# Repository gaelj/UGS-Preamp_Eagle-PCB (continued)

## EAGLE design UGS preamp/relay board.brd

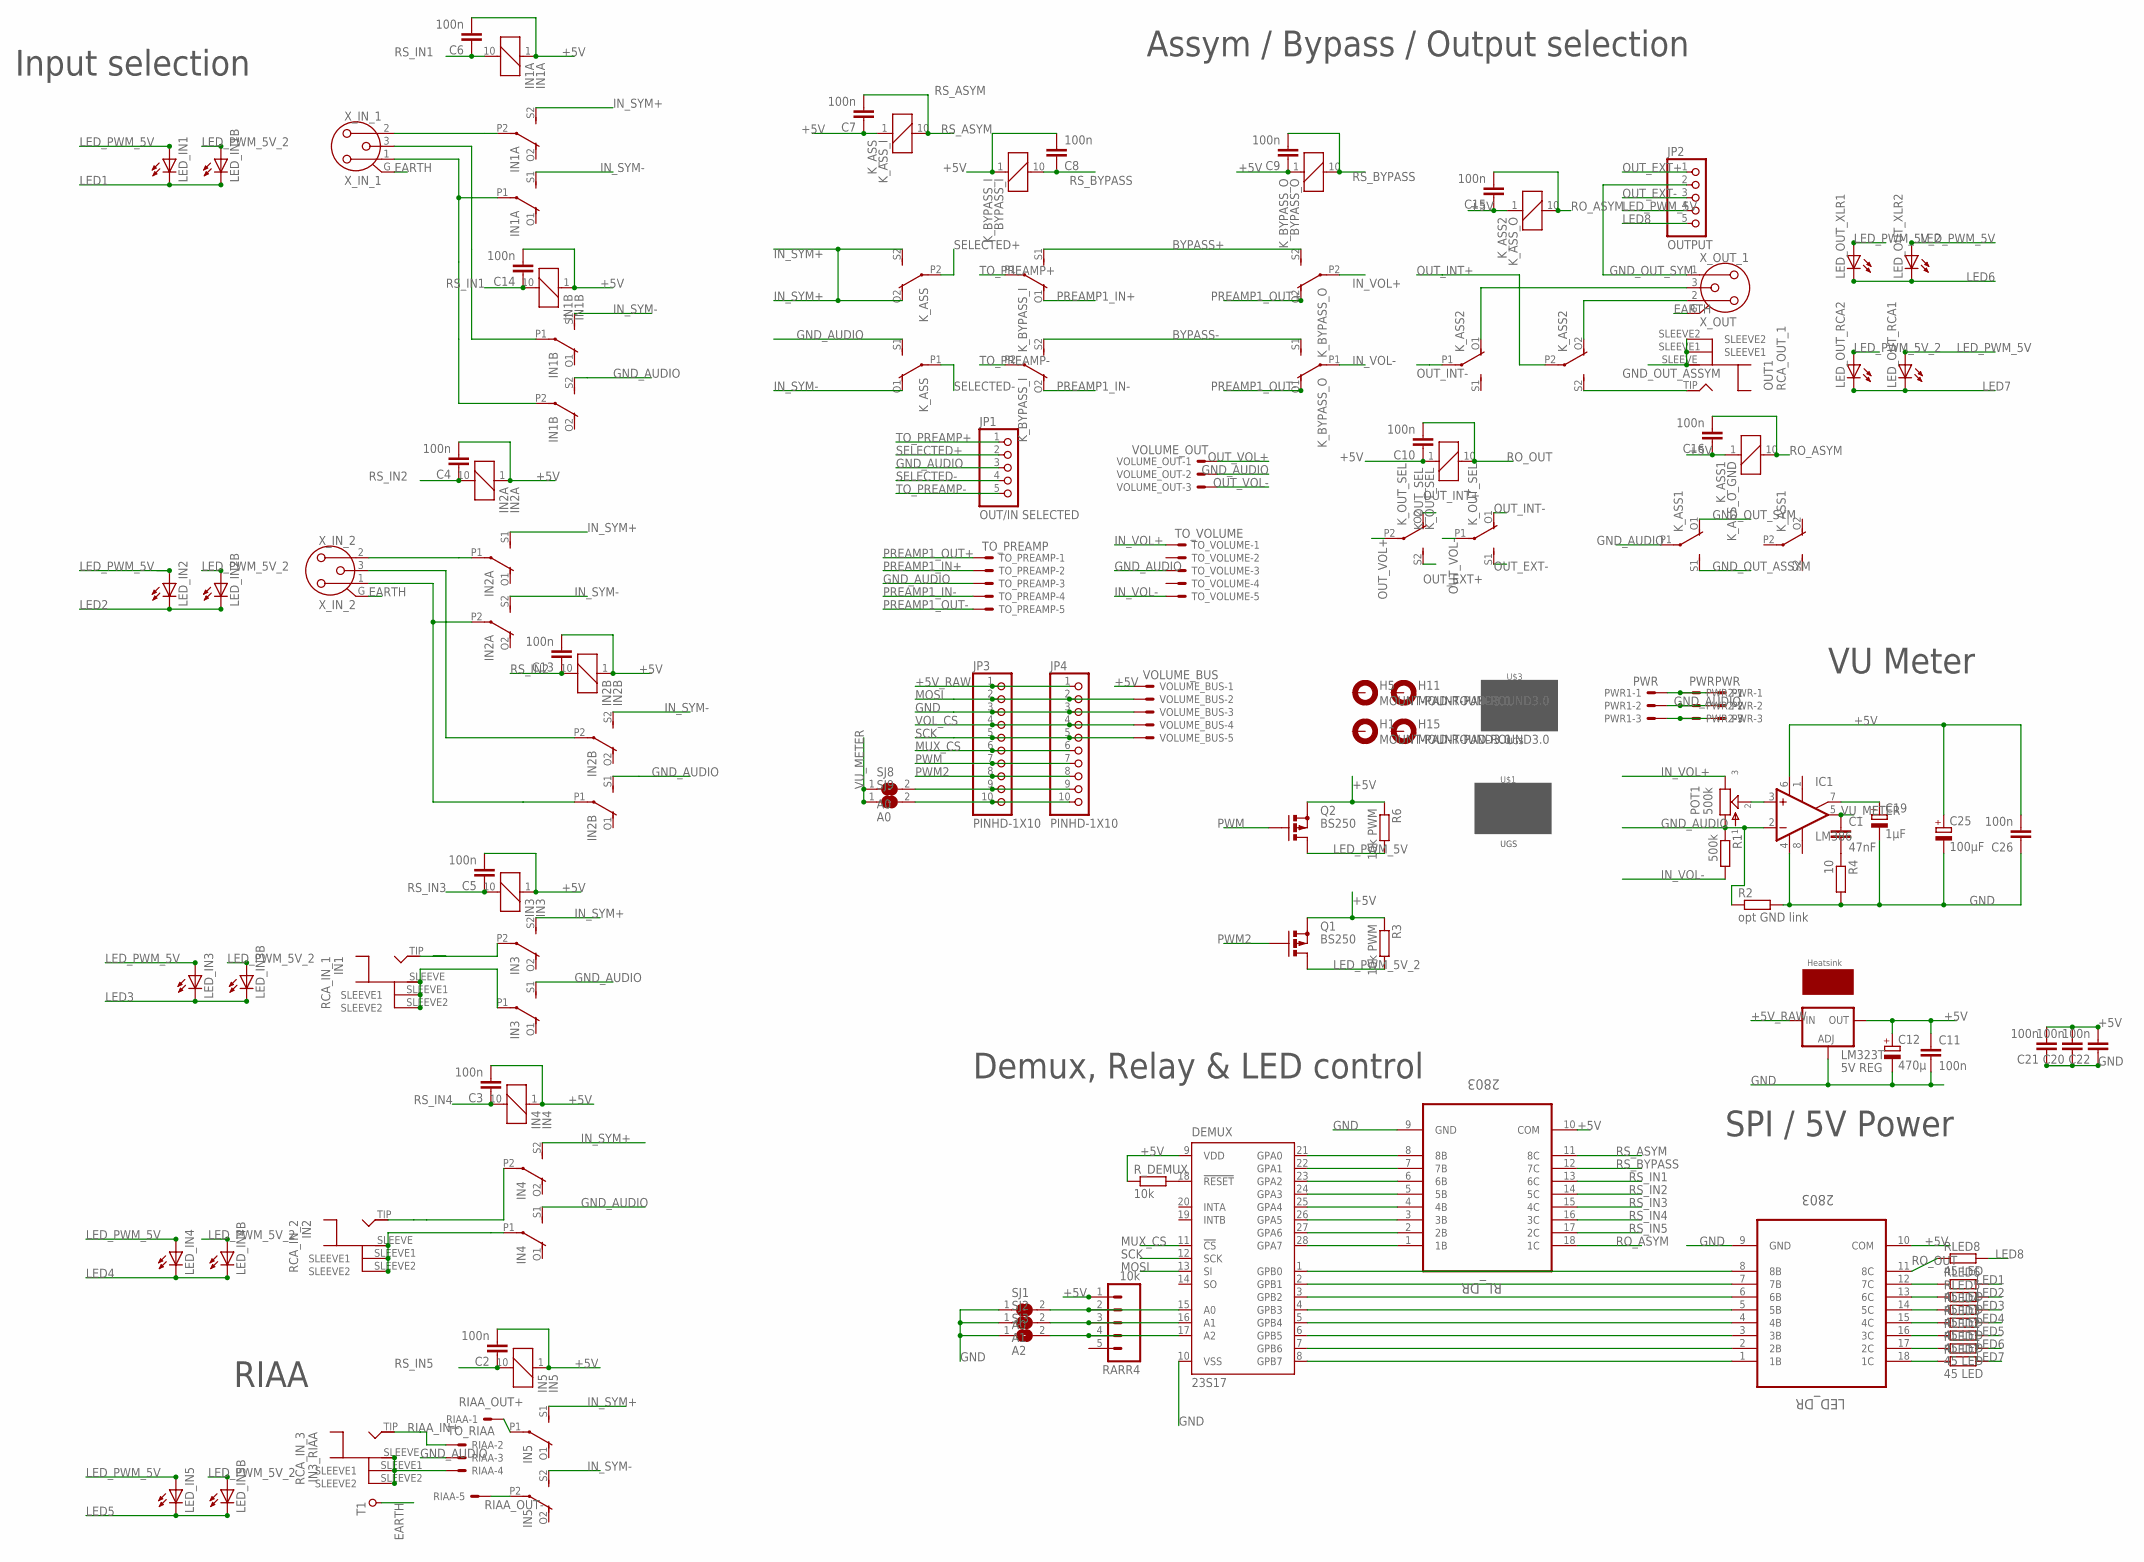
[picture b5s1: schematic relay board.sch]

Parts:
C1: 47nF; C5B3
C2, C3, C4, C5, C6, C7, C8, C9, C10, C11, C13, C14, C15, C16, C20, C21, C22, C26: 100n; C050-025X075
C12: 470µ; E2,5-6
C19: 1µF; E2,5-5
C25: 100µF; E5-6
DEMUX: 23S17; SO28W; MPN MCP23S17-E/SO
H1, H5, H11, H15: MOUNT-PAD-ROUND3.0; 3,0-PAD
IC1: LM386; DIL08
IN1A: IN1A; G6H2-100
IN1B: IN1B; G6H2-100
IN2A: IN2A; G6H2-100
IN2B: IN2B; G6H2-100
IN3: IN3; G6H2-100
IN4: IN4; G6H2-100
IN5: IN5; G6H2-100
JP1: OUT/IN SELECTED; 1X05
JP2: OUTPUT; 1X05
JP3, JP4: PINHD-1X10; 1X10-BIG
K_ASS: K_ASS_I; G6H2-100
K_ASS1: K_ASS_O_GND; G6H2-100
K_ASS2: K_ASS_O; G6H2-100
K_BYPASS_I: BYPASS_I; G6H2-100
K_BYPASS_O: BYPASS_O; G6H2-100
K_OUT_SEL: K_OUT_SEL; G6H2-100
LED_DR: 2803; SOIC127P1030X265-18N; MPN ULN2803ADWR
LED_IN1, LED_IN1B, LED_IN2, LED_IN2B, LED_IN3, LED_IN3B, LED_IN4, LED_IN4B, LED_IN5, LED_IN5B: TLLG4400; LED3MM
LED_OUT_RCA1, LED_OUT_RCA2: TLLG4400; LED3MM
LED_OUT_XLR1, LED_OUT_XLR2: TLLG4400; LED3MM
LM323T: 5V REG; TO220S
POT1: 500k; B25P
PWR, PWR1, PWR2: PWR; 70543-03
Q1, Q2: BS250; SOT54E
R1: 500k; 0207/7
R2: opt GND link; 0207/10
R3, R6: 10k PWM; 0207/10
R4: 10; 0207/10
RARR4: 10k; 1X05
RCA_IN_1: IN1; MONO_JACK
RCA_IN_2: IN2; MONO_JACK
RCA_IN_3: IN3_RIAA; MONO_JACK
RCA_OUT_1: OUT1; MONO_JACK
RIAA: TO_RIAA; 70543-05
RLED1, RLED2, RLED3, RLED4, RLED5, RLED6, RLED7, RLED8: 45 LED; 0207/10
RL_DR: 2803; SOIC127P1030X265-18N
R_DEMUX: 10k; RTH025W
SJ1, SJ8, SJ9: A0; SJ
SJ2: A1; SJ
SJ3: A2; SJ
T1: PAD_TERMINAL-1.02MM_SQUARE; CON_PAD_SQUARE_1.02MM
TO_PREAMP: TO_PREAMP; 70543-05
TO_VOLUME: TO_VOLUME; 70543-05
U$1, U$3: UGS
U$4: HEATSINK
VOLUME_BUS: VOLUME_BUS; 70543-05
VOLUME_OUT: VOLUME_OUT; 70543-03
X_IN_1: X_IN_1; NC3FAH2
X_IN_2: X_IN_2; NC3FAH2
X_OUT_1: X_OUT; NC3MBH

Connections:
+5V: C2.2, C3.2, C4.2, C5.2, C6.2, C7.1, C8.2, C9.1, C10.1, C11.1, C12.+, C13.2, C14.2, C15.1, C16.1, C20.2, C21.2, C22.2, C25.+, C26.2, DEMUX.9 (VDD), IC1.6 (V+), IN1A.1, IN1B.1, IN2A.1, IN2B.1, IN3.1, IN4.1, IN5.1, K_ASS.1, K_ASS1.1, K_ASS2.1, K_BYPASS_I.1, K_BYPASS_O.1, K_OUT_SEL.1, LED_DR.10 (COM), LM323T.3 (OUT), Q1.S, Q2.S, R3.1, R6.1, RARR4.1, RL_DR.10 (COM), R_DEMUX.1, VOLUME_BUS.1
+5V_RAW: JP3.1, JP4.1, LM323T.1 (IN)
BYPASS+: K_BYPASS_I.S1 (S), K_BYPASS_O.S2 (S)
BYPASS-: K_BYPASS_I.S2 (S), K_BYPASS_O.S1 (S)
EARTH: T1.P, X_IN_1.G, X_IN_2.G, X_OUT_1.G
GND: C11.2, C12.-, C19.-, C20.1, C21.1, C22.1, C25.-, C26.1, DEMUX.10 (VSS), IC1.4 (V-), JP3.3, JP4.3, LED_DR.9 (GND), LM323T.2 (ADJ), R2.2, R4.2, RL_DR.9 (GND), SJ1.1, SJ2.1, SJ3.1, VOLUME_BUS.3
GND_AUDIO: IC1.2 (-IN), IN1B.S2 (S), IN2B.S1 (S), IN3.S1 (S), IN4.S1 (S), JP1.3, K_ASS.S1 (S), K_ASS1.P1, POT1.1, PWR.2, PWR1.2, PWR2.2, R1.1, R2.1, RIAA.3, TO_PREAMP.3, TO_VOLUME.3, VOLUME_OUT.2
GND_IN_RIAA: RCA_IN_3.SLEEVE, RCA_IN_3.SLEEVE1, RCA_IN_3.SLEEVE2, RIAA.4
GND_OUT_ASSYM: K_ASS1.S1 (S), RCA_OUT_1.SLEEVE, RCA_OUT_1.SLEEVE1, RCA_OUT_1.SLEEVE2
GND_OUT_SYM: JP2.2, K_ASS1.O1 (O), X_OUT_1.1
IN_SYM+: IN1A.S2 (S), IN2A.S1 (S), IN3.S2 (S), IN4.S2 (S), IN5.S1 (S), K_ASS.O2 (O), K_ASS.S2 (S)
IN_SYM-: IN1A.S1 (S), IN1B.S1 (S), IN2A.S2 (S), IN2B.S2 (S), IN5.S2 (S), K_ASS.O1 (O)
IN_VOL+: K_BYPASS_O.P2, POT1.3, TO_VOLUME.1
IN_VOL-: K_BYPASS_O.P1, R1.2, TO_VOLUME.5
LED1: LED_IN1.K (C), LED_IN1B.K (C), RLED6.2
LED2: LED_IN2.K (C), LED_IN2B.K (C), RLED5.2
LED3: LED_IN3.K (C), LED_IN3B.K (C), RLED4.2
LED4: LED_IN4.K (C), LED_IN4B.K (C), RLED3.2
LED5: LED_IN5.K (C), LED_IN5B.K (C), RLED2.2
LED6: LED_OUT_XLR1.K (C), LED_OUT_XLR2.K (C), RLED1.2
LED7: LED_OUT_RCA1.K (C), LED_OUT_RCA2.K (C), RLED7.2
LED8: JP2.5, RLED8.2
LED_PWM_5V: JP2.4, LED_IN1.A, LED_IN2.A, LED_IN3.A, LED_IN4.A, LED_IN5.A, LED_OUT_RCA1.A, LED_OUT_XLR2.A, Q2.D, R6.2
LED_PWM_5V_2: LED_IN1B.A, LED_IN2B.A, LED_IN3B.A, LED_IN4B.A, LED_IN5B.A, LED_OUT_RCA2.A, LED_OUT_XLR1.A, Q1.D, R3.2
MOSI: DEMUX.13 (SI), JP3.2, JP4.2, VOLUME_BUS.2
MUX_CS: DEMUX.11 (!CS), JP3.6, JP4.6
unnamed: DEMUX.18 (!RESET), R_DEMUX.2
unnamed: LED_DR.17 (2C), RLED1.1
unnamed: IN3.P2, RCA_IN_1.TIP
unnamed: C1.2, R4.1
unnamed: PWR.1, PWR1.1, PWR2.1
unnamed: LED_DR.18 (1C), RLED7.1
unnamed: IC1.3 (+IN), POT1.2
unnamed: LED_DR.16 (3C), RLED2.1
unnamed: C19.+, IC1.7 (BYPASS)
unnamed: JP3.10, JP4.10, SJ9.2
unnamed: DEMUX.8 (GPB7), LED_DR.1 (1B)
unnamed: DEMUX.7 (GPB6), LED_DR.2 (2B)
unnamed: DEMUX.6 (GPB5), LED_DR.3 (3B)
unnamed: DEMUX.5 (GPB4), LED_DR.4 (4B)
unnamed: DEMUX.4 (GPB3), LED_DR.5 (5B)
unnamed: DEMUX.3 (GPB2), LED_DR.6 (6B)
unnamed: DEMUX.2 (GPB1), LED_DR.7 (7B)
unnamed: DEMUX.1 (GPB0), LED_DR.8 (8B)
unnamed: LED_DR.15 (4C), RLED3.1
unnamed: PWR.3, PWR1.3, PWR2.3
unnamed: IN4.P1, RCA_IN_2.SLEEVE, RCA_IN_2.SLEEVE1, RCA_IN_2.SLEEVE2
unnamed: IN2A.P1, X_IN_2.2 (1)
unnamed: IN2B.P2, X_IN_2.3
unnamed: IN2A.P2, IN2B.P1, X_IN_2.1 (2)
unnamed: LED_DR.14 (5C), RLED4.1
unnamed: LED_DR.13 (6C), RLED5.1
unnamed: LED_DR.12 (7C), RLED6.1
unnamed: IN4.P2, RCA_IN_2.TIP
unnamed: DEMUX.15 (A0), RARR4.2, SJ1.2
unnamed: DEMUX.16 (A1), RARR4.3, SJ2.2
unnamed: IN3.P1, RCA_IN_1.SLEEVE, RCA_IN_1.SLEEVE1, RCA_IN_1.SLEEVE2
unnamed: IN1A.P2, X_IN_1.2 (1)
unnamed: IN1B.P1, X_IN_1.3
unnamed: DEMUX.17 (A2), RARR4.4, SJ3.2
unnamed: IN1A.P1, IN1B.P2, X_IN_1.1 (2)
unnamed: K_ASS2.O2 (O), X_OUT_1.2
unnamed: K_ASS2.S2 (S), RCA_OUT_1.TIP
unnamed: DEMUX.21 (GPA0), RL_DR.8 (8B)
unnamed: DEMUX.22 (GPA1), RL_DR.7 (7B)
unnamed: DEMUX.23 (GPA2), RL_DR.6 (6B)
unnamed: DEMUX.24 (GPA3), RL_DR.5 (5B)
unnamed: DEMUX.25 (GPA4), RL_DR.4 (4B)
unnamed: DEMUX.26 (GPA5), RL_DR.3 (3B)
unnamed: DEMUX.27 (GPA6), RL_DR.2 (2B)
unnamed: DEMUX.28 (GPA7), RL_DR.1 (1B)
unnamed: K_ASS2.O1 (O), X_OUT_1.3
unnamed: JP3.9, JP4.9, SJ8.2
OUT_EXT+: JP2.1, K_OUT_SEL.S2 (S)
OUT_EXT-: JP2.3, K_OUT_SEL.S1 (S)
OUT_INT+: K_ASS2.P2, K_OUT_SEL.O2 (O)
OUT_INT-: K_ASS2.P1, K_OUT_SEL.O1 (O)
OUT_VOL+: K_OUT_SEL.P2, VOLUME_OUT.1
OUT_VOL-: K_OUT_SEL.P1, VOLUME_OUT.3
PREAMP1_IN+: K_BYPASS_I.O1 (O), TO_PREAMP.2
PREAMP1_IN-: K_BYPASS_I.O2 (O), TO_PREAMP.4
PREAMP1_OUT+: K_BYPASS_O.O2 (O), TO_PREAMP.1
PREAMP1_OUT-: K_BYPASS_O.O1 (O), TO_PREAMP.5
PWM: JP3.7, JP4.7, Q2.G
PWM2: JP3.8, JP4.8, Q1.G
RIAA_IN+: RCA_IN_3.TIP, RIAA.2
RIAA_OUT+: IN5.P1, RIAA.1
RIAA_OUT-: IN5.P2, RIAA.5
RO_ASYM: C15.2, C16.2, K_ASS1.10 (2), K_ASS2.10 (2), RL_DR.18 (1C)
RO_OUT: C10.2, K_OUT_SEL.10 (2), LED_DR.11 (8C), RLED8.1
RS_ASYM: C7.2, K_ASS.10 (2), RL_DR.11 (8C)
RS_BYPASS: C8.1, C9.2, K_BYPASS_I.10 (2), K_BYPASS_O.10 (2), RL_DR.12 (7C)
RS_IN1: C6.1, C14.1, IN1A.10 (2), IN1B.10 (2), RL_DR.13 (6C)
RS_IN2: C4.1, C13.1, IN2A.10 (2), IN2B.10 (2), RL_DR.14 (5C)
RS_IN3: C5.1, IN3.10 (2), RL_DR.15 (4C)
RS_IN4: C3.1, IN4.10 (2), RL_DR.16 (3C)
RS_IN5: C2.1, IN5.10 (2), RL_DR.17 (2C)
SCK: DEMUX.12 (SCK), JP3.5, JP4.5, VOLUME_BUS.5
SELECTED+: JP1.2, K_ASS.P2
SELECTED-: JP1.4, K_ASS.P1
TO_PREAMP+: JP1.1, K_BYPASS_I.P1
TO_PREAMP-: JP1.5, K_BYPASS_I.P2
VOL_CS: JP3.4, JP4.4, VOLUME_BUS.4
VU_METER: C1.1, IC1.5 (OUT), SJ8.1, SJ9.1

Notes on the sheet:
Assym / Bypass / Output selection
SPI / 5V Power
Demux, Relay & LED control
Input selection
RIAA
VU Meter

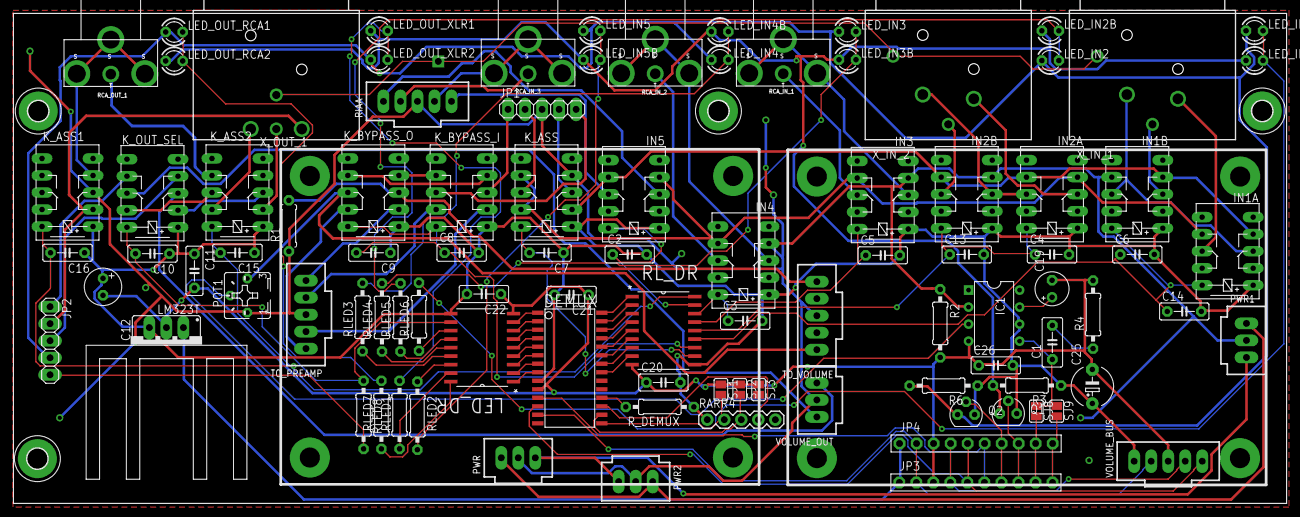
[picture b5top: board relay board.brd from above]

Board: 2 copper layers, 190.1 x 73.2 mm, 104 parts (0 on the bottom side), 104 nets.

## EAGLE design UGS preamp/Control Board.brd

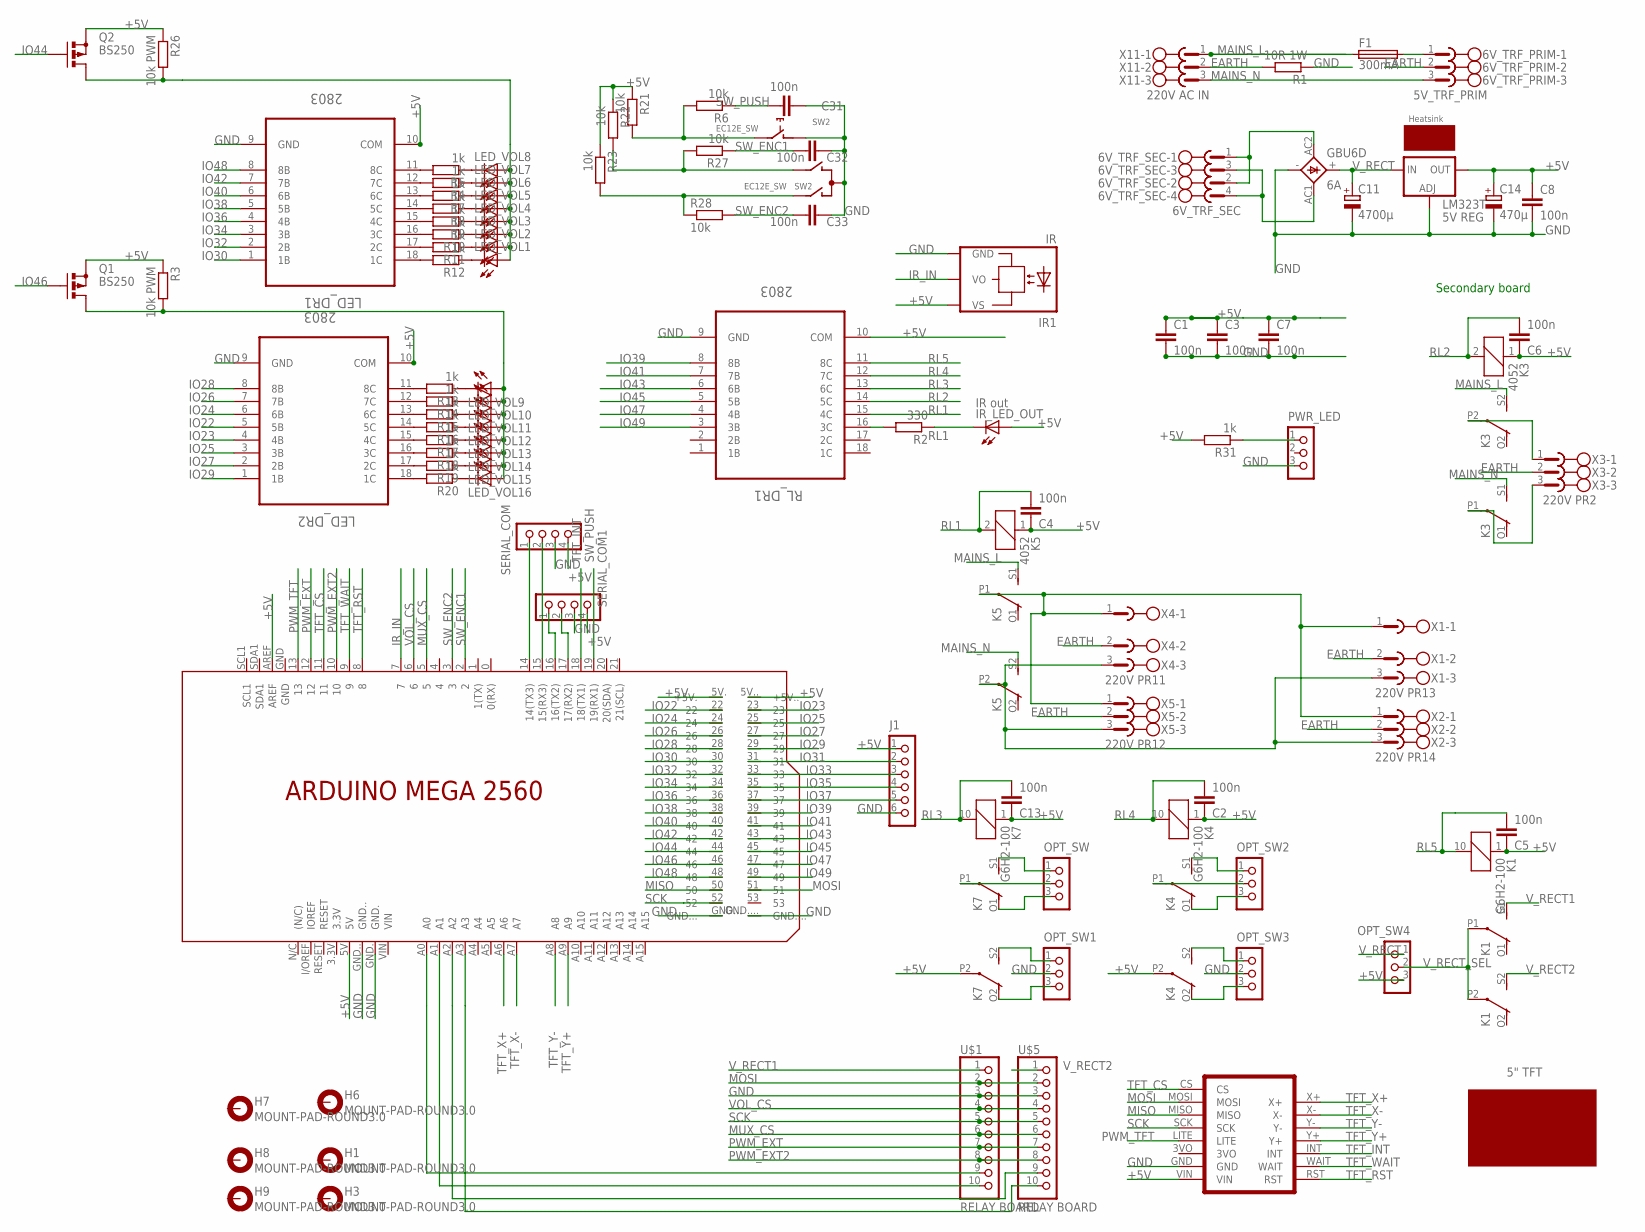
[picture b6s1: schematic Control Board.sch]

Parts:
6V_TRF_PRIM: 5V_TRF_PRIM; MSTBV3; MPN MSTBV 2,5/3-GF-5.08
6V_TRF_SEC: 6V_TRF_SEC; MSTBV4
C1, C2, C3, C4, C5, C6, C7, C8, C13, C31, C32, C33: 100n; C050-025X075
C11: 4700µ; E7,5-16
C14: 470µ; E2,5-6
F1: 300mA; GSH15
GBU6D: 6A; GBU4S
H1, H3, H6, H7, H8, H9: MOUNT-PAD-ROUND3.0; 3,0-PAD
IR1: IR; TSOP17_TB1
IR_LED_OUT: IR out; LED3MM
J1: CON_HEADER_1X06-PTH; M1X6
K1, K4, K7: G6H2-100
K3, K5: 4052; F4052
LED_DR1, LED_DR2: 2803; SOIC127P1030X265-18N; MPN ULN2803ADWR
LED_VOL1, LED_VOL2, LED_VOL3, LED_VOL4, LED_VOL5, LED_VOL6, LED_VOL7, LED_VOL8, LED_VOL9, LED_VOL10, LED_VOL11, LED_VOL12, LED_VOL13, LED_VOL14, LED_VOL15, LED_VOL16: TLLG4400; LED3MM
LM323T: 5V REG; TO220S
OPT_SW, OPT_SW1, OPT_SW2, OPT_SW3: CON_HEADER_1X03-PTH; M1X3
OPT_SW4: V_RECT_-_5V_OUT; M1X3
PCB2: ARDUINO_MEGA2560_INV
PWR_LED: CON_HEADER_1X03-PTH; M1X3
Q1, Q2: BS250; SOT54E
R1: 10R 1W; 0411/15
R2: 330; 0207/10
R3, R26: 10k PWM; 0207/10
R4, R5, R7, R8, R9, R10, R11, R12, R13, R14, R15, R16, R17, R18, R19, R20, R31: 1k; 0207/10
R6, R21, R22, R23, R27, R28: 10k; 0207/10
RL_DR1: 2803; SOIC127P1030X265-18N; MPN ULN2803ADWR
SERIAL_COM, SERIAL_COM1: CON_HEADER_1X04; M1X4
SW2: EC12E_SW; ALPS_EC12E_SW
U$1, U$5: RELAY BOARD; 1X10-BIG
U$2: HEATSINK
U$3: RA8875
U$4: 5"TFT; 5_TFT
X1: 220V PR13; MSTBV3
X2: 220V PR14; MSTBV3; MPN MSTBV 2,5/3-GF-5.08
X3: 220V PR2; MSTBV3
X4: 220V PR11; MSTBV3; MPN MSTBV 2,5/3-GF-5.08
X5: 220V PR12; MSTBV3; MPN MSTBV 2,5/3-GF-5.08
X11: 220V AC IN; MSTBV3

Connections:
+5V: C1.1, C2.1, C3.1, C4.1, C5.1, C6.1, C7.1, C8.1, C13.1, C14.+, IR1.VS, IR_LED_OUT.A, J1.1, K1.1, K3.1, K4.1, K4.P2, K5.1, K7.1, K7.P2, LED_DR1.10 (COM), LED_DR2.10 (COM), LM323T.3 (OUT), OPT_SW4.3, PCB2.5V, PCB2.5V. (+5V.), PCB2.5V.. (+5V..), PCB2.AREF, Q1.S, Q2.S, R3.1, R21.1, R22.1, R23.1, R26.1, R31.2, RL_DR1.10 (COM), SERIAL_COM.4, SERIAL_COM1.4, U$3.VIN
EARTH: 6V_TRF_PRIM.2, R1.2, X1.2, X2.2, X3.2, X4.2, X5.2, X11.2
GND: C1.2, C3.2, C7.2, C8.2, C11.-, C14.-, C31.1, C32.1, C33.1, GBU6D.-, IR1.GND, J1.6, LED_DR1.9 (GND), LED_DR2.9 (GND), LM323T.2 (ADJ), OPT_SW1.2, OPT_SW3.2, PCB2.GND., PCB2.GND.., PCB2.GND..., PCB2.GND...., PWR_LED.3, R1.1, RL_DR1.9 (GND), SERIAL_COM.3, SERIAL_COM1.3, SW2.C, SW2.D (1), U$1.3, U$3.GND, U$5.3
IO22: LED_DR2.5 (5B), PCB2.22
IO23: LED_DR2.4 (4B), PCB2.23
IO24: LED_DR2.6 (6B), PCB2.24
IO25: LED_DR2.3 (3B), PCB2.25
IO26: LED_DR2.7 (7B), PCB2.26
IO27: LED_DR2.2 (2B), PCB2.27
IO28: LED_DR2.8 (8B), PCB2.28
IO29: LED_DR2.1 (1B), PCB2.29
IO30: LED_DR1.1 (1B), PCB2.30
IO31: J1.2, PCB2.31
IO32: LED_DR1.2 (2B), PCB2.32
IO33: J1.3, PCB2.33
IO34: LED_DR1.3 (3B), PCB2.34
IO35: J1.4, PCB2.35
IO36: LED_DR1.4 (4B), PCB2.36
IO37: J1.5, PCB2.37
IO38: LED_DR1.5 (5B), PCB2.38
IO39: PCB2.39, RL_DR1.8 (8B)
IO40: LED_DR1.6 (6B), PCB2.40
IO41: PCB2.41, RL_DR1.7 (7B)
IO42: LED_DR1.7 (7B), PCB2.42
IO43: PCB2.43, RL_DR1.6 (6B)
IO44: PCB2.44, Q2.G
IO45: PCB2.45, RL_DR1.5 (5B)
IO46: PCB2.46, Q1.G
IO47: PCB2.47, RL_DR1.4 (4B)
IO48: LED_DR1.8 (8B), PCB2.48
IO49: PCB2.49, RL_DR1.3 (3B)
IR_IN: IR1.VO, PCB2.7
LED_COMMON_1: LED_VOL1.A, LED_VOL2.A, LED_VOL3.A, LED_VOL4.A, LED_VOL5.A, LED_VOL6.A, LED_VOL7.A, LED_VOL8.A, Q2.D, R26.2
LED_COMMON_2: LED_VOL9.A, LED_VOL10.A, LED_VOL11.A, LED_VOL12.A, LED_VOL13.A, LED_VOL14.A, LED_VOL15.A, LED_VOL16.A, Q1.D, R3.2
MAINS_L: F1.1, K3.S2 (S), K5.S1 (S), X11.1
MAINS_N: 6V_TRF_PRIM.3, K3.S1 (S), K5.S2 (S), X11.3
MISO: PCB2.50, U$3.MISO
MOSI: PCB2.51, U$1.2, U$3.MOSI, U$5.2
MUX_CS: PCB2.5, U$1.6, U$5.6
unnamed: K4.P1, OPT_SW2.2
unnamed: R2.2, RL_DR1.16 (3C)
unnamed: IR_LED_OUT.K (C), R2.1
unnamed: LED_VOL1.K (C), R12.1
unnamed: PCB2.14 (14(TX3)), SERIAL_COM.1
unnamed: PCB2.15 (15(RX3)), SERIAL_COM.2
unnamed: LED_DR1.11 (8C), R5.2
unnamed: K4.S1 (S), OPT_SW2.1
unnamed: K4.O1 (O), OPT_SW2.3
unnamed: LED_VOL2.K (C), R11.1
unnamed: R6.2, R21.2, SW2.E (2)
unnamed: LED_VOL3.K (C), R10.1
unnamed: LED_VOL4.K (C), R9.1
unnamed: LED_VOL5.K (C), R8.1
unnamed: LED_VOL6.K (C), R7.1
unnamed: LED_VOL7.K (C), R4.1
unnamed: LED_VOL8.K (C), R5.1
unnamed: LED_DR2.11 (8C), R13.2
unnamed: LED_DR2.12 (7C), R14.2
unnamed: LED_DR2.13 (6C), R15.2
unnamed: LED_DR2.14 (5C), R16.2
unnamed: LED_DR2.15 (4C), R17.2
unnamed: LED_DR2.16 (3C), R18.2
unnamed: LED_DR2.17 (2C), R19.2
unnamed: LED_DR2.18 (1C), R20.2
unnamed: K7.S2 (S), OPT_SW1.1
unnamed: R22.2, R27.2, SW2.B
unnamed: LED_DR1.12 (7C), R4.2
unnamed: LED_DR1.13 (6C), R7.2
unnamed: K7.P1, OPT_SW.2
unnamed: LED_DR1.14 (5C), R8.2
unnamed: LED_DR1.15 (4C), R9.2
unnamed: LED_DR1.16 (3C), R10.2
unnamed: LED_DR1.17 (2C), R11.2
unnamed: LED_DR1.18 (1C), R12.2
unnamed: 6V_TRF_SEC.3, 6V_TRF_SEC.4, GBU6D.AC1 (AC2)
unnamed: 6V_TRF_SEC.1, 6V_TRF_SEC.2, GBU6D.AC2 (AC1)
unnamed: K7.O2 (O), OPT_SW1.3
unnamed: LED_VOL9.K (C), R13.1
unnamed: LED_VOL10.K (C), R14.1
unnamed: LED_VOL11.K (C), R15.1
unnamed: LED_VOL12.K (C), R16.1
unnamed: LED_VOL13.K (C), R17.1
unnamed: LED_VOL14.K (C), R18.1
unnamed: K3.P1, X3.3
unnamed: LED_VOL15.K (C), R19.1
unnamed: LED_VOL16.K (C), R20.1
unnamed: K7.S1 (S), OPT_SW.1
unnamed: PCB2.16 (16(TX2)), SERIAL_COM1.1
unnamed: PCB2.17 (17(RX2)), SERIAL_COM1.2
unnamed: R23.2, R28.1, SW2.A
unnamed: K4.S2 (S), OPT_SW3.1
unnamed: K3.P2, X3.1
unnamed: 6V_TRF_PRIM.1, F1.2
unnamed: K7.O1 (O), OPT_SW.3
unnamed: PCB2.A0, U$1.9
unnamed: PCB2.A1, U$1.10
unnamed: PCB2.A2, U$5.9
unnamed: PCB2.A3, U$5.10
unnamed: K4.O2 (O), OPT_SW3.3
unnamed: PWR_LED.1, R31.1
unnamed: K5.P1, X1.1, X2.1, X4.1, X5.1
unnamed: K5.P2, X1.3, X2.3, X4.3, X5.3
PWM_EXT: PCB2.12, U$1.7, U$5.7
PWM_EXT2: PCB2.10, U$1.8, U$5.8
PWM_TFT: PCB2.13, U$3.LITE
RL1: C4.2, K5.2, RL_DR1.15 (4C)
RL2: C6.2, K3.2, RL_DR1.14 (5C)
RL3: C13.2, K7.10 (2), RL_DR1.13 (6C)
RL4: C2.2, K4.10 (2), RL_DR1.12 (7C)
RL5: C5.2, K1.10 (2), RL_DR1.11 (8C)
SCK: PCB2.52, U$1.5, U$3.SCK, U$5.5
SW_ENC1: C32.2, PCB2.2, R27.1
SW_ENC2: C33.2, PCB2.3, R28.2
SW_PUSH: C31.2, PCB2.19 (19(RX1)), R6.1
TFT_CS: PCB2.11, U$3.CS
TFT_INT: PCB2.18 (18(TX1)), U$3.INT
TFT_RST: PCB2.8, U$3.RST
TFT_WAIT: PCB2.9, U$3.WAIT
TFT_X+: PCB2.A6, U$3.X+
TFT_X-: PCB2.A7, U$3.X-
TFT_Y+: PCB2.A9, U$3.Y+
TFT_Y-: PCB2.A8, U$3.Y-
VOL_CS: PCB2.6, U$1.4, U$5.4
V_RECT: C11.+, GBU6D.+, LM323T.1 (IN), OPT_SW4.1
V_RECT1: K1.S1 (S), U$1.1
V_RECT2: K1.S2 (S), U$5.1
V_RECT_SEL: K1.P1, K1.P2, OPT_SW4.2

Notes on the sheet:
Secondary board

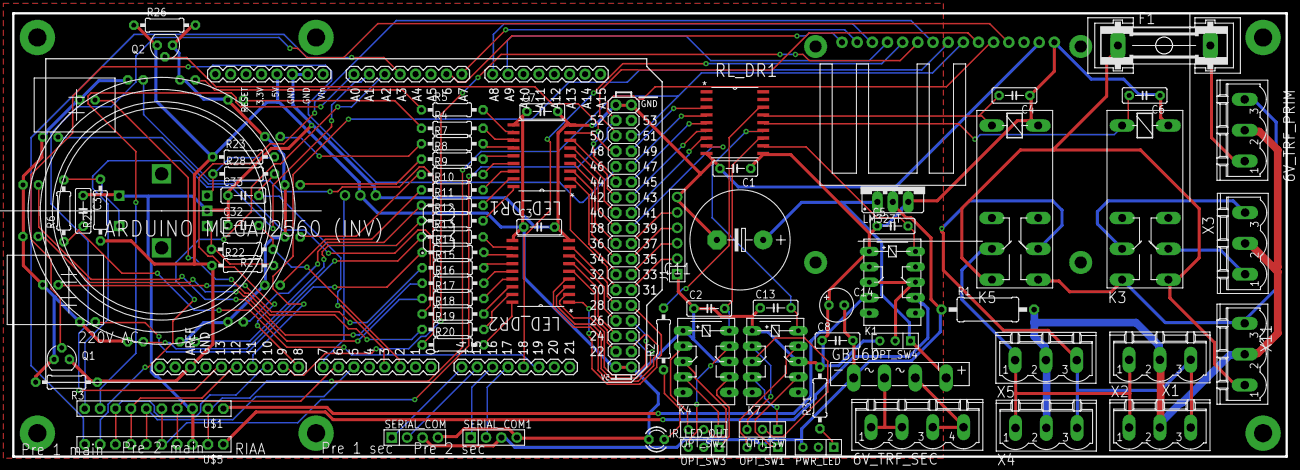
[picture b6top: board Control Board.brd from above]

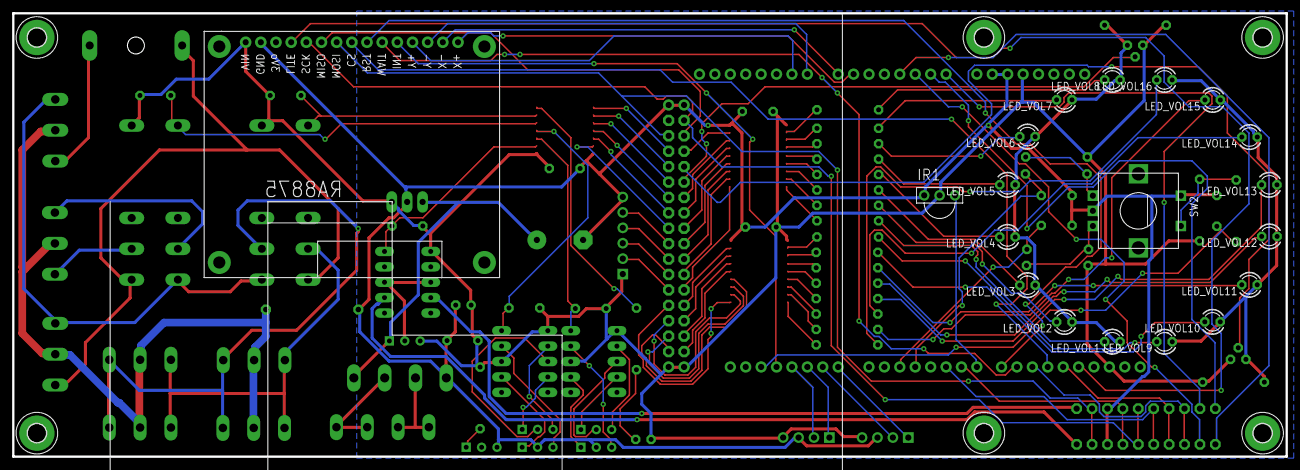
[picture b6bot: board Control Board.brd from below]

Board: 2 copper layers, 209.9 x 73.1 mm, 102 parts (24 on the bottom side), 127 nets.

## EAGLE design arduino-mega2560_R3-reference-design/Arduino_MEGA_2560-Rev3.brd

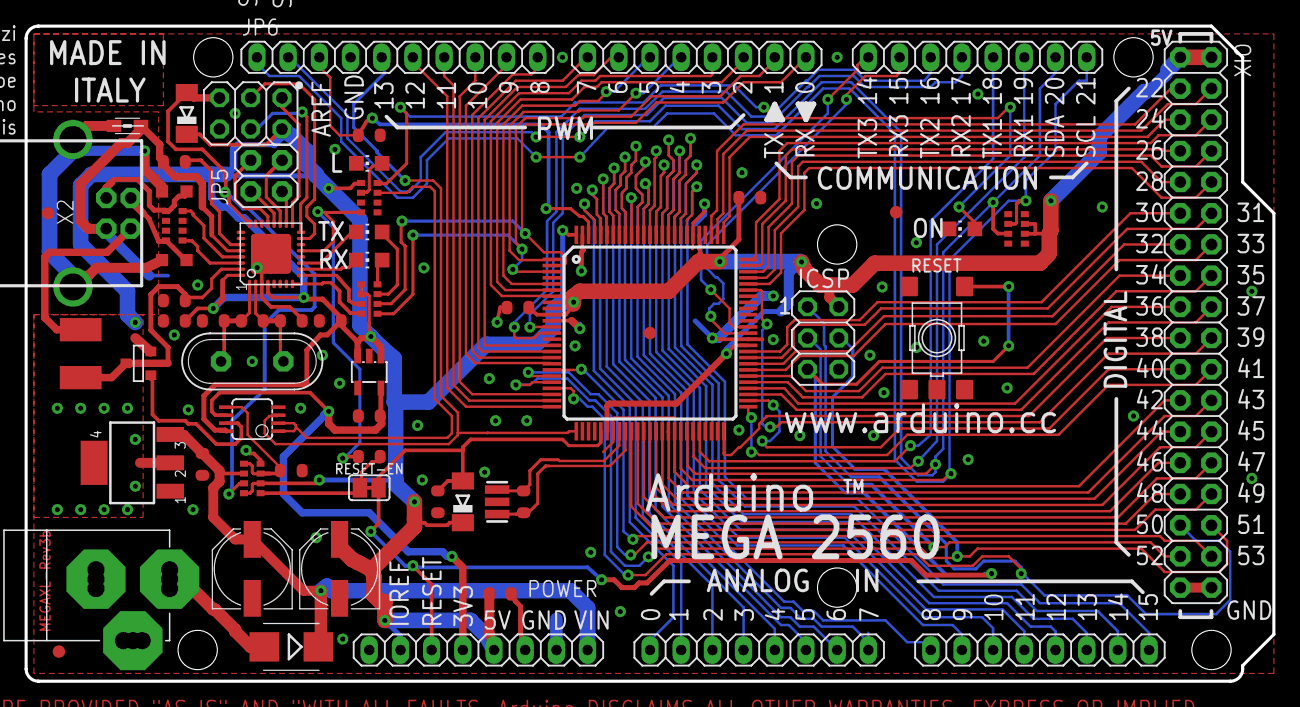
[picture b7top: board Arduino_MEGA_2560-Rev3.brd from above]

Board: 2 copper layers, 101.6 x 53.3 mm, 63 parts (1 on the bottom side), 110 nets.

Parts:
ADCH: 8x1F-H8.5; 1X08
ADCL: 8x1F-H8.5; 1X08
C1, C14, C15: 22p; C0603-ROUND
C2, C3, C4, C5, C6, C7, C8, C9, C11, C12: 100n; C0603-ROUND
C10, C13: 1u; C0603-ROUND
COMMUNICATION: 8x1F-H8.5; 1X08
D1: M7; SMB
D2, D3: CD1206-S01575; MINIMELF
F1: MF-MSMF050-2 500mA; L1812
FD1, FD2, FD3, FD4: FIDUCIALMOUNT; FIDUCIA-MOUNT
GROUND: SJ
IC1: NCP1117ST50T3G; SOT223
IC3: ATMEGA2560-16AU; TQFP100
IC4: ATMEGA16U2-MU; MLF32
IC6: LP2985-33DBVR; SOT23-DBV
IC7: LMV358IDGKR; MSOP08
ICSP, ICSP1: 3x2M; 2X03
JP5: 2x2M - NM; 2X02
JP6: 10x1F-H8.5; 1X10
L: YELLOW; CHIP-LED0805
L1: BLM21; 0805
ON: GREEN; CHIP-LED0805
PC1, PC2: 47u; PANASONIC_D
POWER: 8x1F-H8.5; 1X08
PWML: 8x1F-H8.5; 1X08
R1, R2: 1M; R0603-ROUND
RESET: TS42031-160R-TR-7260; TS42
RESET-EN: SJ
RN1, RN5: 10K; CAT16
RN2: 22R; CAY16
RN3, RN4: 1k; CAY16
RX: YELLOW; CHIP-LED0805
T1: FDN340P; SOT-23
TX: YELLOW; CHIP-LED0805
U$1: DISCLAIMER
X1: POWERSUPPLY_DC21MMX; POWERSUPPLY_DC-21MM
X2: USB-B_TH; PN61729
XIO: 18x2F-H8.5; 2X18
Y1: CSTCE16M0V53-R0 16MHZ; RESONATOR
Y2: 16MHz; QS
Z1, Z2: CG0603MLC-05E; CT/CN0603

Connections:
8PB4: IC4.18, JP5.1
8PB5: IC4.19, JP5.3
8PB6: IC4.20, JP5.2
8PB7: IC4.21, JP5.4
+3V3: C13.2, IC6.5, IC7.6, POWER.4
+5V: C4.1, C5.1, C6.1, C9.1, C11.2, D2.C, D3.C, IC1.2, IC1.4, IC3.10, IC3.31, IC3.61, IC3.80, IC3.100, IC4.4, IC4.32, IC6.1, IC6.3, IC7.8, ICSP.2, ICSP1.2, PC2.+, POWER.2, POWER.5, RN1.6, RN1.7, RN3.1, RN4.5, RN4.6, RN5.2, RN5.8, T1.2, XIO.1, XIO.2
ADC0: ADCL.1, IC3.97
ADC1: ADCL.2, IC3.96
ADC2: ADCL.3, IC3.95
ADC3: ADCL.4, IC3.94
ADC4: ADCL.5, IC3.93
ADC5: ADCL.6, IC3.92
ADC6: ADCL.7, IC3.91
ADC7: ADCL.8, IC3.90
ADC8: ADCH.1, IC3.89
ADC9: ADCH.2, IC3.88
ADC10: ADCH.3, IC3.87
ADC11: ADCH.4, IC3.86
ADC12: ADCH.5, IC3.85
ADC13: ADCH.6, IC3.84
ADC14: ADCH.7, IC3.83
ADC15: ADCH.8, IC3.82
AREF: C3.1, IC3.98, JP6.3
CMP: C12.2, IC7.5, RN5.3, RN5.5
D+: RN2.5, X2.3, Z2.2
D-: RN2.8, X2.2, Z1.2
DTR: C7.1, IC4.13, RN3.4
GATE_CMD: IC7.7, T1.3
GND: C1.2, C2.2, C3.2, C4.2, C5.2, C6.2, C8.2, C9.2, C11.1, C12.1, C13.1, C14.2, C15.2, GROUND.2, IC1.1, IC3.11, IC3.32, IC3.62, IC3.81, IC3.99, IC4.3, IC4.33, IC6.2, IC7.4, ICSP.6, ICSP1.6, JP6.4, L.C, ON.C, PC1.-, PC2.-, POWER.6, POWER.7, RESET.1, RESET.2, RN3.5, RN5.4, X1.1, X1.3, XIO.35, XIO.36, Y1.2
L13: IC7.1, IC7.2, RN3.7
M8RXD: IC4.9, RN4.7
M8TXD: IC4.8, RN4.8
MISO2: IC4.17, ICSP1.1
MOSI2: IC4.16, ICSP1.4
unnamed: L.A, RN3.2
unnamed: ON.A, RN3.8
unnamed: RN4.4, RX.A
unnamed: RN4.3, TX.A
PA0: IC3.78, XIO.3
PA1: IC3.77, XIO.4
PA2: IC3.76, XIO.5
PA3: IC3.75, XIO.6
PA4: IC3.74, XIO.7
PA5: IC3.73, XIO.8
PA6: IC3.72, XIO.9
PA7: IC3.71, XIO.10
PB0: IC3.19, XIO.34
PB1: IC3.20, ICSP.3, XIO.33
PB2: IC3.21, ICSP.4, XIO.32
PB3: IC3.22, ICSP.1, XIO.31
PB4: IC3.23, JP6.8
PB5: IC3.24, JP6.7
PB6: IC3.25, JP6.6
PB7: IC3.26, IC7.3, JP6.5
PC0: IC3.53, XIO.18
PC1: IC3.54, XIO.17
PC2: IC3.55, XIO.16
PC3: IC3.56, XIO.15
PC4: IC3.57, XIO.14
PC5: IC3.58, XIO.13
PC6: IC3.59, XIO.12
PC7: IC3.60, XIO.11
PD7: IC3.50, XIO.19
PE0: IC3.2, PWML.1, RN4.2
PE1: IC3.3, PWML.2, RN4.1
PE3: IC3.5, PWML.6
PE4: IC3.6, PWML.3
PE5: IC3.7, PWML.4
PG0: IC3.51, XIO.22
PG1: IC3.52, XIO.21
PG2: IC3.70, XIO.20
PG5: IC3.1, PWML.5
PH3: IC3.15, PWML.7
PH4: IC3.16, PWML.8
PH5: IC3.17, JP6.10
PH6: IC3.18, JP6.9
PL0: IC3.35, XIO.30
PL1: IC3.36, XIO.29
PL2: IC3.37, XIO.28
PL3: IC3.38, XIO.27
PL4: IC3.39, XIO.26
PL5: IC3.40, XIO.25
PL6: IC3.41, XIO.24
PL7: IC3.42, XIO.23
PWRIN: D1.A, X1.2
RD+: IC4.29, RN2.4
RD-: IC4.30, RN2.1
RESET: C1.1, C7.2, D3.A, IC3.30, ICSP.5, POWER.3, RESET.3, RESET.4, RESET-EN.1, RESET-EN.2, RN5.1
RESET2: D2.A, IC4.24, ICSP1.5, RN5.7
RXD1: COMMUNICATION.3, IC3.45
RXD2: COMMUNICATION.5, IC3.12
RXD3: COMMUNICATION.7, IC3.63
RXL: IC4.10, RX.C
SCK2: IC4.15, ICSP1.3
SCL: COMMUNICATION.1, IC3.43, JP6.1, RN1.2
SDA: COMMUNICATION.2, IC3.44, JP6.2, RN1.3
TXD1: COMMUNICATION.4, IC3.46
TXD2: COMMUNICATION.6, IC3.13
TXD3: COMMUNICATION.8, IC3.64
TXL: IC4.11, TX.C
UGND: C10.2, GROUND.1, IC4.28, L1.1, X2.4
USBVCC: C8.1, F1.1, IC4.31, T1.1
USHIELD: L1.2, X2.P$1, X2.P$2, Z1.1, Z2.1
VIN: C2.1, D1.C, IC1.3, PC1.+, POWER.8, RN5.6
VUCAP: C10.1, IC4.27
XT1: C14.1, IC4.1, R2.1, Y2.2
XT2: C15.1, IC4.2, R2.2, Y2.1
XTAL1: IC3.34, R1.1, Y1.3
XTAL2: IC3.33, R1.2, Y1.1
XVCC: F1.2, X2.1
